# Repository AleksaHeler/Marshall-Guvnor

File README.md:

# Marshall Guvn'or guitar effect pedal

My attempt at recreating this pedal. Using KiCAD for schematic and PCB design, as well as online reference of the effect schematic.

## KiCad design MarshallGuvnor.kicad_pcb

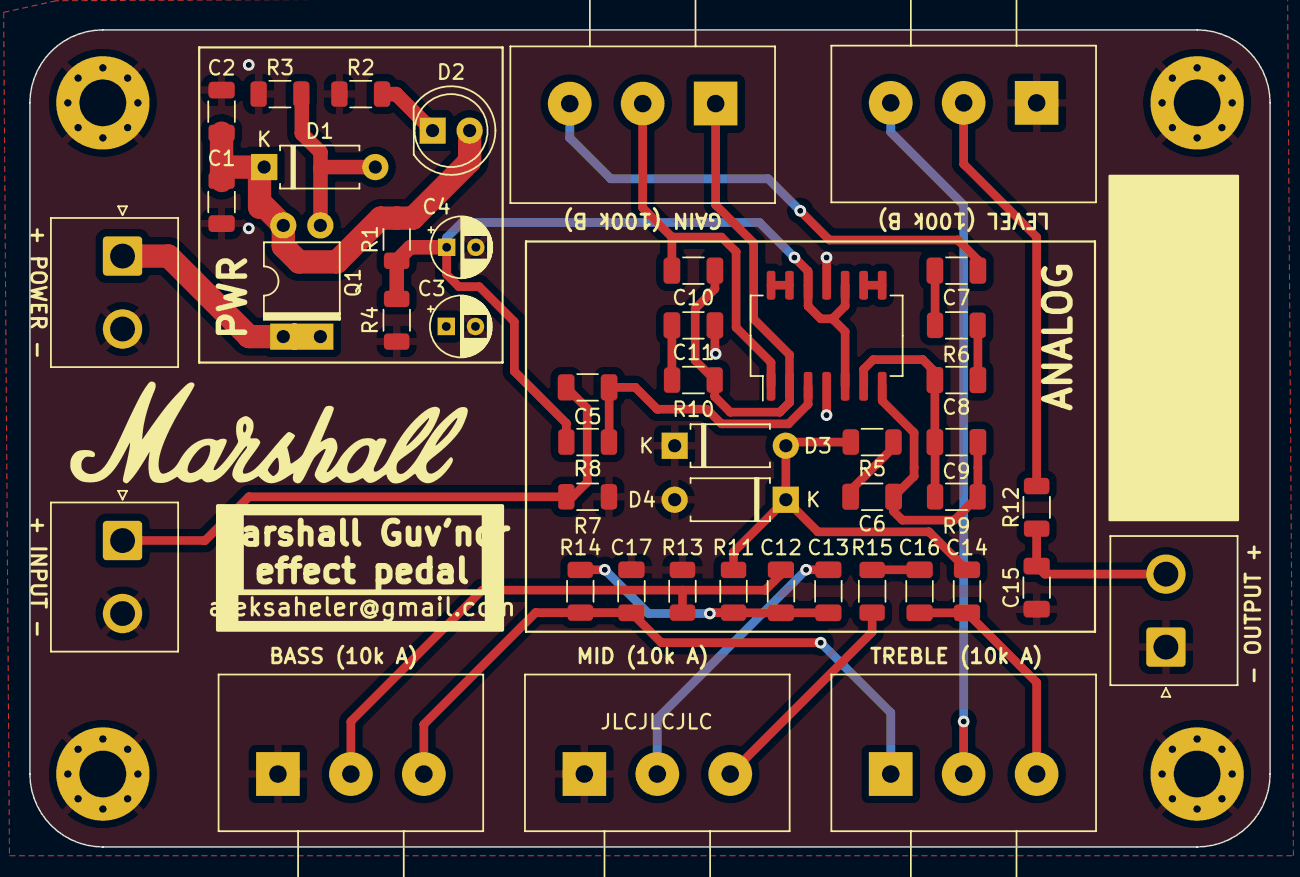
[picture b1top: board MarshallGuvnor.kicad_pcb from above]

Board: 4 copper layers, 85.0 x 56.0 mm, 50 parts (0 on the bottom side), 30 nets.

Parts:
C1: 1u; C_1206_3216Metric
C2, C8, C11, C12: 100n; C_1206_3216Metric
C3: 100uF; CP_Radial_D4.0mm_P2.00mm
C4: 47uF; CP_Radial_D4.0mm_P2.00mm
C5, C10, C16: 10n; C_1206_3216Metric
C6, C7, C13: 220n; C_1206_3216Metric
C9: 220pf; C_1206_3216Metric
C14: 4n; C_1206_3216Metric
C15: 470p; C_1206_3216Metric
C17: 68n; C_1206_3216Metric
D1: D_Zener; D_A-405_P7.62mm_Horizontal
D2: RED; LED_D5.0mm_FlatTop
D3, D4: 1N4007; D_A-405_P7.62mm_Horizontal
H1, H2, H3, H4: MountingHole_Pad; MountingHole_3.2mm_M3_Pad_Via
J1: POWER; JST_NV_B02P-NV_1x02_P5.00mm_Vertical
J2: INPUT; JST_NV_B02P-NV_1x02_P5.00mm_Vertical
J3: OUTPUT; JST_NV_B02P-NV_1x02_P5.00mm_Vertical
Q1: IRFD9120 PMOS; Vishay_HVM-DIP-3_W7.62mm
R1, R4: 47k; R_1206_3216Metric
R2: 470; R_1206_3216Metric
R3, R15: 100; R_1206_3216Metric
R5: 1k; R_1206_3216Metric
R6: 10k; R_1206_3216Metric
R7: 2M2; R_1206_3216Metric
R8: 1M; R_1206_3216Metric
R9: 680k; R_1206_3216Metric
R10: 2k2; R_1206_3216Metric
R11: 1k5; R_1206_3216Metric
R12: 22k; R_1206_3216Metric
R13, R14: 680; R_1206_3216Metric
RV1: GAIN_100k_B; Potentiometer_Alps_RK163_Single_Horizontal
RV2: LVL_100k_B; Potentiometer_Alps_RK163_Single_Horizontal
RV3: Mid_10k_A; Potentiometer_Alps_RK163_Single_Horizontal
RV4: Bass_10k_A; Potentiometer_Alps_RK163_Single_Horizontal
RV5: Treble_10k_A; Potentiometer_Alps_RK163_Single_Horizontal
U1: TL084; SO-14_5.3x10.2mm_P1.27mm

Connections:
+4V: C4.1, R1.1, R4.2, R8.2, U1.5 (+), U1.10 (+), U1.12 (+)
+9V: C1.2, C2.2, C3.1, D1.1 (K), D2.2 (A), Q1.3 (S), R1.2, U1.4 (V+)
DISTORSION_OUT: C14.2, D3.2 (A), D4.1 (K), R5.2, R11.1
GND: C1.1, C2.1, C3.2, C4.2, C11.1, C15.1, C17.2, D3.1 (K), D4.2 (A), H1.1, H2.1, H3.1, H4.1, J1.2, J2.2, J3.1, R2.1, R3.1, R4.1, R7.2, R13.1, RV2.1, RV3.1, RV4.1, U1.11 (V-)
MIX_OUT: RV2.3, RV5.2
unnamed: C6.1, C9.2, R9.2, U1.7
unnamed: C6.2, R5.1
unnamed: C7.1, RV1.3
unnamed: C7.2, R6.1
unnamed: C8.1, R6.2
unnamed: C10.2, RV1.2, U1.1
unnamed: C11.2, R10.1
unnamed: C12.1, R13.2, RV4.2
unnamed: C12.2, C13.2, R11.2, R14.2
unnamed: C13.1, RV3.2
unnamed: C14.1, C16.2, RV5.3
unnamed: C16.1, R15.1
unnamed: C17.1, R14.1, RV4.3, RV5.1
unnamed: D1.2 (A), Q1.2 (G), R3.2
unnamed: D2.1 (K), R2.2
unnamed: J1.1, Q1.1 (D)
unnamed: C5.1, J2.1, R7.1
unnamed: C15.2, J3.2, R12.2
unnamed: R12.1, RV2.2
unnamed: R15.2, RV3.3
unnamed: C5.2, R8.1, U1.3 (+)
unnamed: C10.1, R10.2, RV1.1, U1.2 (-)
unnamed: C8.2, C9.1, R9.1, U1.6 (-)
unnamed: U1.8, U1.9 (-)
unnamed: U1.13 (-), U1.14

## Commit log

2024-01-13 closed kicad
2024-02-11 Minor bugfixes
2024-10-19 Added pics
2025-05-09 Update shcm, change one cap value, add footswitch
